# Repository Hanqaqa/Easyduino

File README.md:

# Easyduino: Repository of Open Source PCB Devboards for KiCad

The Easyduino project is an effort to easily dive into different PCB designs of the most popular microcontroller devboards like **Arduino, ESP32, Raspberry Pico and STM32 Bluepill** (more to come!). Using the free and Open Source Software [KiCad](https://www.kicad.org/) and adhering the best practices across the PCB and KiCad ecosystem. Also adding the much needed USB-C support!

The project was born out of the necessity to unify the wide variety of software, languages and conventions used in the most popular devboards. For example Arduino Uno was developed in 2010, Italy, using Eagle. The ESP32 devboard was developed in 2016, China, using Altium. The Raspberry Pi Pico 2040 was developed around 2021 in the U.K. using KiCad and Altium...

## Available Development Boards 

[Easyduino UNO](https://github.com/Hanqaqa/Easyduino/tree/master/Atmega328p%20Arduino%20Uno) | [Easyduino Nano](https://github.com/Hanqaqa/Easyduino/tree/master/Atmega328p%20Arduino%20Nano) | [Easyduino ESP32](https://github.com/Hanqaqa/Easyduino/tree/master/ESP32) |
---|---|---|
 |  |  | 

[Easyduino ESP32 S3](https://github.com/Hanqaqa/Easyduino/tree/master/ESP32S3) | [Easyduino Pi Pico](https://github.com/Hanqaqa/Easyduino/tree/master/Raspberry%20Pi%20Pico%202040) | [Easyduino Bluepill STM32F103](https://github.com/Hanqaqa/Easyduino/tree/master/STM32F103%20Bluepill)
---|---|---|
 |  | 

[Easyduino Pi Pico 2](https://github.com/Hanqaqa/Easyduino/tree/master/PiPico2) | [Easyduino Pi Pico 2 2354B](https://github.com/Hanqaqa/Easyduino/tree/master/PiPico22354B) | [Easyduino nrf52840 dongle](https://github.com/Hanqaqa/Easyduino/tree/master/nrf52840dongle)
---|---|---|
 |  | 

The outline, pinout, layout and components have been tried to be replicated with respect to the originals, in all of the boards. With various levels of success. 

Some boards, like the Raspberry Pi Pico use 01005 components which are too expensive for the manufacturer to integrate in the PCB Aseembly line. Some other components like the original Arduino UNO USB to Serial converter, an Atmega16u2, were hard to come by during the development of this project ~January 2023, so more readily available options were chosen. All the differences with the original boards are explained inside the folder of each project in a readme file. 

4 layers of copper have been used in all projects to simplify the wiring. Specifically the [JLC04161H-7628](https://jlcpcb.com/impedance) stackup. 

The PCB constraints of the manufacturer JLCPCB are explained [here](https://github.com/Hanqaqa/Easyduino/tree/master/Assets/JLCPCB%20Constraints)

## Structure of each project

Each project consists of: 
- Main KiCad files (.kicad_pro, .kicad_sch...)
- A readme explaining the specifics of that project
- xxx.pretty or xxxlibraries folder which contains the non standard footprints or schematic parts used in the project (Some projects such as the Arduino UNO only use standard libraries, therefore these folders don't exist)
- The **Outputs** folder: Contains all the data produced by the KiCad Jobset like Gerbers, STEPs, PDFs, ERC, BOM, CPLs... Most of these are then copied, organized, and placed into their respective `ProductionFiles` folders.
- The ***ProductionFiles*** folder which includes files such as:
    - BOM: This folder contains both the list of components and the Centroid File in JLCPCB readable format. The CPL .csv file needs a small tweak at the beginning of the file in order to be readable. I mention it [here](https://github.com/Hanqaqa/Easyduino/tree/master/Assets/JLCPCB%20Constraints#cpl-component-placement-list).
    - ***Datasheets***: all the datasheets of the main components used in the project. Datasheets of easily replaceable components such as Resistors, Capacitors and LEDs are not given
    - Gerbers: A zip file with all of the manufacturing gerber files such as Copper/Mask/Silkscreen layers
    - PDFs: PDF and PNG files of the Schematic and PCB
    - Photos: Some photos of the manufactured PCB as well as some renders

## Using the project

1. Install the latest version of [KiCad](https://www.kicad.org/)
2. If you already have KiCad installed, click the upper right button in this github page `<>Code`, click `Download ZIP`, extract the files in your desired folder. If you know how to use git, clone the repository
3. Double click on the xxx.kicad_pro file inside any project and KiCad will start

This project was developed using KiCad v8.0.0, but has been updated and tested with KiCad v10. Including the creation of Jobsets which massively simplfies creating gerbers and BOMs. 

Since this is a collection of projects, the new KiCad v10 Git utilities don't work properly with each project, forcing you to git add the whole project if you want to make a change.

If you'd rather just consult the schematics or the gerbers. They are located inside the **ProductionFiles** folder of each project. Inside the **PDFs** and **Gerber** folders.

## Contributing

If you spot any mistakes inside any of the projects. Either open an issue and I will try to correct it or fork and merge the correction. 

If you plan on developing any other development boards and wish to merge into the project. Please try to use the same style and conventions as the original ones in the schematic. Positive voltages facing up, text being clearly readable, a references page, similar folder structure.

To do list:

- [ ] ~~Order and test the v1.1 RP2040 board. (In v1.0 I mixed some pins in the Flash and couldn't boot up). Ordered. Awaiting arrival. v1.1 is working correctly. Need to update photos and repo.~~ Order v1.2 with Silkscreen text for BOOTSEL and RESET. Once received test and make photos.
- [ ] ~~Order and test the v1.1 ESP32S3 board. (In v1.0 I forgot to add PullUp and PullDown in RST and SUSPEND CP2102). Ordered. Awaiting arrival.~~ TX and RX signals going into CP2102 were mixed. Fix it and order v1.2. Once received test and make photos.
- [ ] Developing: nRF52840 Dongle, RP2350A (Pi Pico 2), and Pi Pico 2 2354B with extra functionalities
- [ ] Investigate other possible microcontrollers/SOCs/FPGAs to implement.

## Acknowledgments

Thanks to [winsrrow](https://github.com/winsrrow) for providing lots of KiCad tips and designing from the ground up the v1.1 RP2040 board.

## Licensing

This project is distributed under the [**CERN Open Hardware Licence Version 2 - Permissive**](https://github.com/Hanqaqa/Easyduino/blob/master/License.txt) which means **you are free to use any or all parts of this project with or without disclosing the source**, even for comercial projects. As long as you include a copy of the CERN OHLv2 Permissive Licence.

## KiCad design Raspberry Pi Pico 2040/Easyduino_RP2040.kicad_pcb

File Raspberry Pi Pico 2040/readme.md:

# Raspberry Pi Pico RP2040 v1.2 IN PROGRESS.

The new and easy to use Microcontroller from the Raspberry Pi Foundation. Now with a Reset button. Connect via USB, hold BOOTSEL (BT), press and release RESET(RST), then release BOOTSEL. You are now in Bootloader mode.

**The pictured version is v1.0 which had some pins mixed up in the flash memory and couldn't boot up. The project contains the v1.2 which corrects that mistake, adds a debug port and some test points. The photo will be updated when I receive and test the new board.**
**The mounting holes are not exactly in the same position as the original Pi Pico due to the size of USBC**

## Schematic

KiCad's "Net classes" have been used in this schematic (The squares and romboids in the schematic). Net classes are useful for organising different nets on the circuit. For example, you can change all tracks widths for that net in just one menu.

## Gerbers

## Specs

- Input Voltage: 5.5V-9V(External Source 5V) or 5V (USB). ONLY USE ONE VOLTAGE INPUT AT A TIME
- Maximum Output Current at 5V input : 200 mA at 3.3V output
- No Polarity Protection (External Source)
- Overcurrent Protection: None! 

## References 

### RP2040

- RPI Pico Schematic
- Hardware design with rp2040 p10 -> 12MHz crystal with 27 pF Capacitors 
- rp2040 datasheet p13 -> USB_DP and USB_DM need 27 Ohm Resistors
- rp2040 datasheet p13 -> Use a 12MHz Crystal
- rp2040 datasheet p13 -> TESTEN to GND
- rp2040 datasheet p155 -> USB_VDD connected to 3.3V and decoupled with a 100 nF capacitor
- rp2040 datasheet p155 -> IOVDD connected to 3.3V and decoupled with a 100 nF capacitor per pin (6pins)
- rp2040 datasheet p155 -> DVDD connected to VREG_VOUT = 1.1V and decoupled with a 100 nF capacitor per pin (2pins)
- rp2040 datasheet p156 -> ADC_AVDD connected to 3.3V and decoupled with a 100 nF capacitor. A better circuit (Pico Schematic) can be made when ADC is crucial
- rp2040 datasheet p160 -> VREG_VIN Internal 1.1V Voltage regulator Input. Connect to external 3.3V and decouple with 1uF
- rp2040 datasheet p160 -> VREG_VOUT Internal 1.1V Voltage regulator Output. Connect to 1.1V and decouple with 1uF

### USB-C

#### Differential Pair

- USB needs 90 Ohm differential traces. 
- According to JLCPCB impedance calculator, with a JLC7628 prepreg and 6mil (0.15mm) space between lines
- I have to use 9 mil tracks -> 0.2 mm
- I have to place vias because of the pinout of USB C and CP2102. Some other people have done it with no problems

### W25Q16JVUXIQ

- W25Q16JVUXIQ Datasheet p6 -> Use a 100nF and 1uF capacitor
- RPI Pico Schematic -> Use a 100nF and 2uF decoupling capacitors. A pull up resistor is not fitted
- Hardware design with rp2040 p9 -> Use a 100nF decoupling capacitor. Pull up resistor is not fitted, the flash can work without it. 
- I will only place the 100nF capacitor, since the devboard can work according to Hardware design guide. I will not place a pull up resitor

### XC6206P332MR-3.3V

- XC6206_Torex Datasheet p6 -> Two 1 uF ceramic capacitors on Vin and Vout

### Differences with Original Raspberry Pi Pico

- GPIO23 is not exposed or used. Since the voltage regulator used (XC6206...) doesn't have a Power Select mode
- GPIO29_ADC which is used for monitoring VSys (external battery) is not exposed or used in order to save costs
- In the Raspberry Pi Pico Schematic, 2uF capacitors are used for decoupling. I use 1uF decoupling capacitors as indicated in the rp2040 datasheet
- ADC_AVDD is powered only by 3.3V, no option for external Analog powering. This will be more noisy for projects where ADC is used. But in order to save space and cost. I will skip the option to power ADC_AVDD externally

## KiCad Render

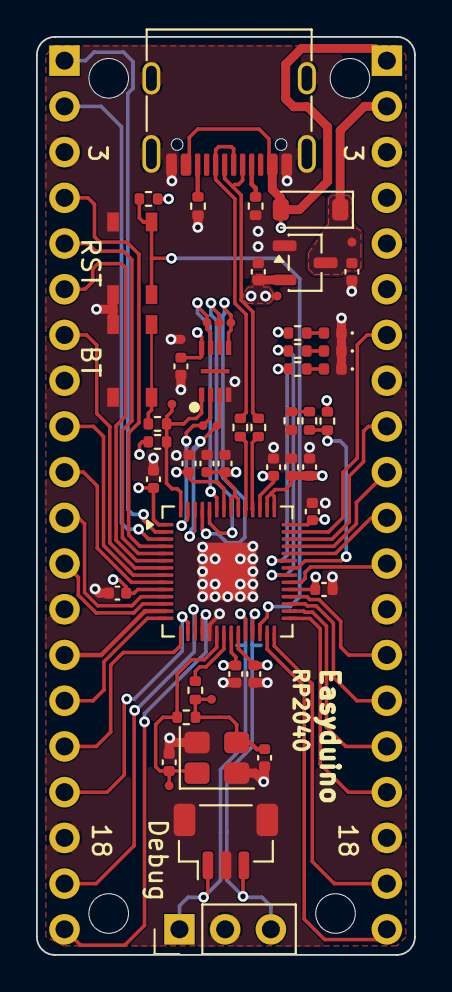
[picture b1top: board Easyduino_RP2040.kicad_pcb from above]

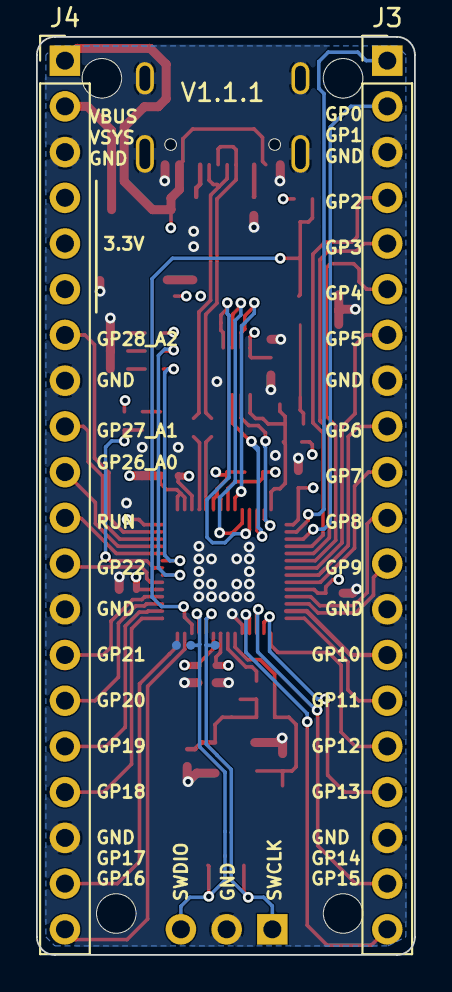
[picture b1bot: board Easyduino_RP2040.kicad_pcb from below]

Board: 4 copper layers, 21.0 x 51.0 mm, 65 parts (5 on the bottom side), 58 nets.

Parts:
C1, C2, C5, C6, C7, C8, C9, C10, C11, C12, C15: 100nF; C_0402_1005Metric
C3, C4, C13, C14: 1uF; C_0402_1005Metric
C16, C17: 27p; C_0402_1005Metric
D1: D_Schottky; D_SOD-123
D2, D3, D4: LED; LED_0402_1005Metric
H1, H2, H3, H4: MountingHole; MountingHole_2.2mm_M2
J1: USB_C_Receptacle_USB2.0; USB_C_Receptacle_G-Switch_GT-USB-7010ASV
J3, J4: Conn_01x20; PinHeader_1x20_P2.54mm_Vertical
J5: Conn_01x03; PinHeader_1x03_P2.54mm_Vertical
J6: Conn_01x03_MountingPin; JST_SH_BM03B-SRSS-TB_1x03-1MP_P1.00mm_Vertical
R1, R2, R3, R6, R7: 5.1k; R_0402_1005Metric
R4, R5: 27R; R_0402_1005Metric
R8, R9, R10, R11, R12, R13, R14, R15: 1k; R_0402_1005Metric
SW1, SW2: SW_Push; ALPSALPINE_SKRPACE010
TP1, TP2, TP3, TP4, TP5, TP6, TP7, TP8, TP9, TP10, TP11, TP12, TP13, TP14: TestPoint_pad
U1: XC6206P332MR; SOT-23-3
U2: RP2040; QFN-56-1EP_7x7mm_P0.4mm_EP3.2x3.2mm
U3: W25Q16JVUXIQ
Y1: 12MHz; Crystal_SMD_3225-4Pin_3.2x2.5mm

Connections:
+1V1: C1.1, C2.1, C3.1, U2.23 (DVDD), U2.45 (VREG_VOUT), U2.50 (DVDD)
+3.3V: C4.1, C5.1, C6.1, C7.1, C8.1, C9.1, C10.1, C11.1, C12.1, C14.1, C15.1, J4.4, J4.5, J4.6, R10.1, R11.1, R12.1, TP2.1 (1_1), U1.2 (VO), U2.1 (IOVDD), U2.10 (IOVDD), U2.22 (IOVDD), U2.33 (IOVDD), U2.42 (IOVDD), U2.43 (ADC_AVDD), U2.44 (VREG_IN), U2.48 (USB_VDD), U2.49 (IOVDD), U3.8 (VCC)
/CC1: J1.A5 (CC1), R1.1
/CC2: J1.B5 (CC2), R2.1
/GPIO0: J3.1, U2.2 (GPIO0)
/GPIO1: J3.2, U2.3 (GPIO1)
/GPIO2: J3.4, U2.4 (GPIO2)
/GPIO3: J3.5, U2.5 (GPIO3)
/GPIO4: J3.6, U2.6 (GPIO4)
/GPIO5: J3.7, U2.7 (GPIO5)
/GPIO6: J3.9, U2.8 (GPIO6)
/GPIO7: J3.10, U2.9 (GPIO7)
/GPIO8: J3.11, U2.11 (GPIO8)
/GPIO9: J3.12, U2.12 (GPIO9)
/GPIO10: J3.14, U2.13 (GPIO10)
/GPIO11: J3.15, U2.14 (GPIO11)
/GPIO12: J3.16, U2.15 (GPIO12)
/GPIO13: J3.17, U2.16 (GPIO13)
/GPIO14: J3.19, U2.17 (GPIO14)
/GPIO15: J3.20, U2.18 (GPIO15)
/GPIO16: J4.20, U2.27 (GPIO16)
/GPIO17: J4.19, U2.28 (GPIO17)
/GPIO18: J4.17, U2.29 (GPIO18)
/GPIO19: J4.16, U2.30 (GPIO19)
/GPIO20: J4.15, U2.31 (GPIO20)
/GPIO21: J4.14, U2.32 (GPIO21)
/GPIO22: J4.12, U2.34 (GPIO22)
/GPIO23: R13.1, U2.35 (GPIO23)
/GPIO24: R3.1, R6.2, U2.36 (GPIO24)
/GPIO25: R14.1, U2.37 (GPIO25)
/GPIO26_ADC0: J4.11, U2.38 (GPIO26_ADC0)
/GPIO27_ADC1: J4.10, U2.39 (GPIO27_ADC1)
/GPIO28_ADC2: J4.9, U2.40 (GPIO28_ADC2)
/GPIO29_ADC3: J4.7, U2.41 (GPIO29_ADC3)
/LED_3V3: D2.2 (A), R12.2
/LED_BUILT_IN1: D4.2 (A), R14.2
/LED_BUILT_IN2: D3.2 (A), R13.2
/QSPI_SCLK: TP9.1 (1_1), U2.52 (QSPI_SCLK), U3.6 (CLK)
/QSPI_SD0: TP10.1 (1_1), U2.53 (QSPI_SD0), U3.5 (DI(IO0))
/QSPI_SD1: TP11.1 (1_1), U2.55 (QSPI_SD1), U3.2 (DO(IO1))
/QSPI_SD2: TP12.1 (1_1), U2.54 (QSPI_SD2), U3.3 (IO2)
/QSPI_SD3: TP13.1 (1_1), U2.51 (QSPI_SD3), U3.7 (IO3)
/QSPI_SS: R10.2, R15.1, TP8.1 (1_1), U2.56 (QSPI_SS), U3.1 (~CS)
/RDIV: R6.1, R7.2
/RUN: R11.2, SW2.2, U2.26 (RUN)
/SW1_{PULL-UP}: R15.2, SW1.2
/SWCLK: J5.1, J6.1, TP5.1 (1_1), U2.24 (SWCLK)
/SWD: J5.3, J6.3, TP6.1 (1_1), U2.25 (SWD)
/USB_DN: J1.A7 (D-), J1.B7 (D-), R5.1
/USB_DP: J1.A6 (D+), J1.B6 (D+), R4.1
/USB_R_DN: R5.2, U2.46 (USB_DM)
/USB_R_DP: R4.2, U2.47 (USB_DP)
/Xin: C16.1, R8.1, TP3.1 (1_1), U2.20 (XIN), Y1.1
/Xout: R9.2, U2.21 (XOUT)
/XoutR: C17.1, R8.2, R9.1, TP4.1 (1_1), Y1.3
GND: C1.2, C2.2, C3.2, C4.2, C5.2, C6.2, C7.2, C8.2, C9.2, C10.2, C11.2, C12.2, C13.2, C14.2, C15.2, C16.2, C17.2, D2.1 (K), D3.1 (K), D4.1 (K), J1.A1 (GND), J1.A12 (GND), J1.B1 (GND), J1.B12 (GND), J1.SH (SHIELD), J3.3, J3.8, J3.13, J3.18, J4.3, J4.8, J4.13, J4.18, J5.2, J6.2, J6.MP (MountPin), R1.2, R2.2, R7.1, SW1.1, SW2.1, TP7.1 (1_1), TP14.1 (1_1), U1.1 (GND), U2.19 (TESTEN), U2.57 (GND), U3.4 (GND), Y1.2 (G), Y1.4 (G)
VBUS: D1.2 (A), J1.A4 (VBUS), J1.A9 (VBUS), J1.B4 (VBUS), J1.B9 (VBUS), J4.1, R3.2
VCC: C13.1, D1.1 (K), J4.2, TP1.1 (1_1), U1.3 (VI)

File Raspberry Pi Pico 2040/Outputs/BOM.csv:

"Reference","Value","Qty","#","LCSC"
"C1","100nF","1","1","C1525"
"C2","100nF","1","2","C1525"
"C3","1uF","1","3","C52923"
"C4","1uF","1","4","C52923"
"C5","100nF","1","5","C1525"
"C6","100nF","1","6","C1525"
"C7","100nF","1","7","C1525"
"C8","100nF","1","8","C1525"
"C9","100nF","1","9","C1525"
"C10","100nF","1","10","C1525"
"C11","100nF","1","11","C1525"
"C12","100nF","1","12","C1525"
"C13","1uF","1","13","C52923"
"C14","1uF","1","14","C52923"
"C15","100nF","1","15","C1525"
"C16","27p","1","16","C1557"
"C17","27p","1","17","C1557"
"D1","D_Schottky","1","18","C8598"
"D2","LED","1","19","C434448"
"D3","LED","1","20","C434448"
"D4","LED","1","21","C434448"
"H1","MountingHole","1","22","-"
"H2","MountingHole","1","23","-"
"H3","MountingHole","1","24","-"
"H4","MountingHole","1","25","-"
"J1","USB_C_Receptacle_USB2.0","1","26","C2765186"
"J3","Conn_01x20","1","27","-"
"J4","Conn_01x20","1","28","-"
"J5","Conn_01x03","1","29","-"
"J6","Conn_01x03_MountingPin","1","30","C160389"
"R1","5.1k","1","31","C25905"
"R2","5.1k","1","32","C25905"
"R3","5.1k","1","33","C25905"
"R4","27R","1","34","C2909343"
"R5","27R","1","35","C2909343"
"R6","5.1k","1","36","C25905"
"R7","5.1k","1","37","C25905"
"R9","1k","1","38","C11702"
"R12","1k","1","39","C11702"
"R13","1k","1","40","C11702"
"R14","1k","1","41","C11702"
"R15","1k","1","42","C11702"
"SW1","SW_Push","1","43","C139797"
"SW2","SW_Push","1","44","C139797"
"TP1","","1","45",""
"TP2","","1","46",""
"TP3","","1","47",""
"TP4","","1","48",""
"TP5","","1","49",""
"TP6","","1","50",""
"TP7","","1","51",""
"TP8","","1","52",""
"TP9","","1","53",""
"TP10","","1","54",""
"TP11","","1","55",""
"TP12","","1","56",""
"TP13","","1","57",""
"TP14","","1","58",""
"U1","XC6206P332MR","1","59","C347376"
"U2","RP2040","1","60","C2040"
"U3","W25Q16JVUXIQ","1","61","C2843335"
"Y1","12MHz","1","62","C9002"

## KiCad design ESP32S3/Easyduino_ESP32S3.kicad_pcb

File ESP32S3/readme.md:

# ESP32S3 v1.2 IN PROGRESS

The new and powerful microcontroller from Espressif

**The pictured version is v1.0 which had TX/RX from the CP2102 going into the ESP32S3 module mixed up. The project contains the v1.2 which corrects that mistake. Will update the pictures once I order antoher batch and test everything works correctly.**

## Schematic

KiCad Schematic symbols, footprints and 3D Models were obtained from their [KiCad Github repository](https://github.com/espressif/kicad-libraries)

## Gerbers

## Specs

- Input Voltage: 5V-15V(External Source 5V) 5V (USB UART OR USB ESP32) or 3.3V. ONLY USE ONE VOLTAGE INPUT AT A TIME
- Output Current at 3.3V : 1 A (External Source) 500mA (USB)
- No Polarity Protection (External Source)
- Overcurrent Protection: None 

## References 

### ESP32 S3 WROOM 1

#### Decoupling Capacitors:

- ESP32 S3 WROOM 1 datasheet p25 -> 3.3V pin needs a 22uF and a 100nF capacitors. The 22uF doesn't have to be a tantalum capacitor. But I will use a tantalum to reuse components

#### Automatic Bootloader

- ESPS3 Sch -> Automatic Bootloader.
- ESPS3 Sch / ESP32 S3 WROOM 1 datasheet p25 -> EN pin 10k resistor and 100nF capacitor

#### Thermal vias

- ESP32 S3 WROOM 1 datasheet p27 -> GND Thermal needs vias between pads

### USB-C

#### Filtering 

- USB Hardware Design Guidelines for FTDI ICs p8 -> 10nF Cap + Ferrite Bead + 100nF Cap + 4.7uF Cap
- I disregarded such heavy filtering for the easier to implement 1uF and 100nF cap given in the CP2102 datasheet
- I added a polyfuse with Ihold=500mA and Itrip=1A.

#### Differential Pair

- USB needs 90 Ohm differential traces. 
- Using JLCPCB's JLC04161H-7628 stackup.
- Which with Signal Layer (Layer 1) and a GND layer (L2) below. And with 0.2mm tracks and separated 0.15mm gives a differential pair impedance of approximately 90 Ohms.
- For USB1 will use a very short trace for D+ D- (around 2mm)
- For USB2 (tracks that go to the internal ESP32 S3 pins and the pinout) the traces are long ~60mm for D+ D-, and have vias
- The Development board from ESP32S3 has no problem with these differential pairs with vias and is a 2 board layer
- I also have to place vias because of the pinout of USB C and CP2102. Some other people have placed vias without problems for signal integrity

#### CP2102

- CP2102 datasheet p15 -> VBUS will be tied to REGIN. 1uF and 100 nF will be added.
- CP2102 datasheet p15 -> ESD Supression Diode for all three inputs of USB  
- CP2102 datasheet p15 and p19 -> 100nF for VDD output, 4.7 uF is optional for higher current circuits.
- CP2102 datasheet p23 -> The VDD or 3.3 output can only provide 100mA. I will not use this as a voltage provider for the ciruit. I will use the AMS1117-3.3 
- CP2102 datasheet p15 -> RST pulled up via 4.7k and SUSPEND~ pulled down via 10k.

#### AMS1117-3.3V

- AMS1117 Datasheet p1 -> 3.3V/1A Output with 5-15V Input
- AMS1117 Datasheet p4 -> 22uF tantalum capacitor on input and output.

## KiCad Render

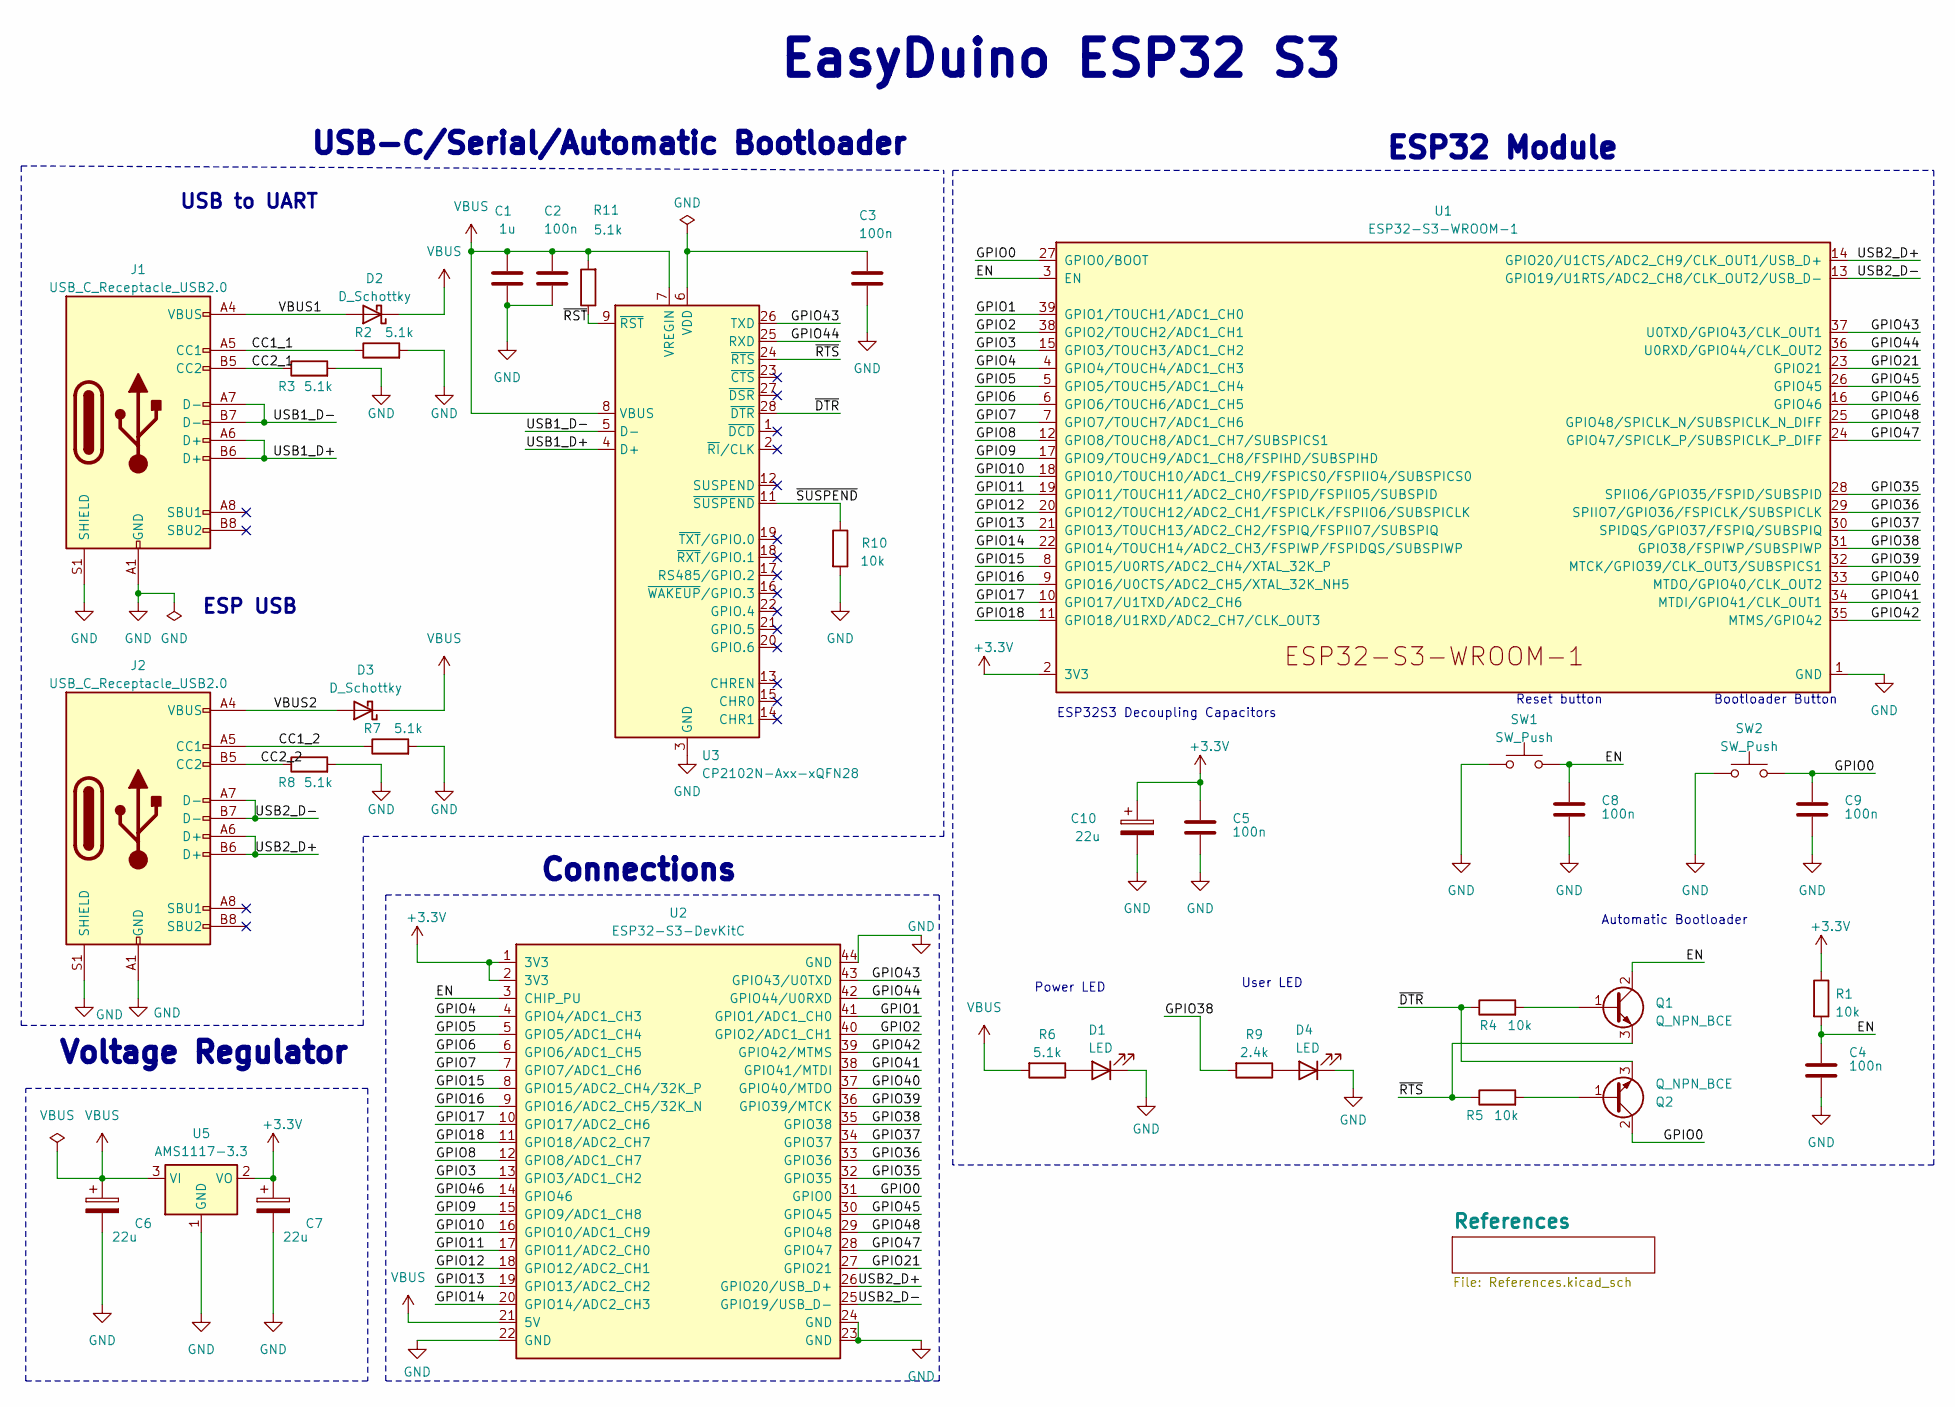
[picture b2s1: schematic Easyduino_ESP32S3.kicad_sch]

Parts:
C1: 1u; C_0402_1005Metric; LCSC C52923
C2, C3, C4, C5, C8, C9: 100n; C_0402_1005Metric; LCSC C1525
C6, C7, C10: 22u; CP_EIA-3216-10_Kemet-I; LCSC C11366
D1, D4: LED; LED_0402_1005Metric; LCSC C434447
D2, D3: D_Schottky; D_0402_1005Metric; LCSC C2837790
J1, J2: USB_C_Receptacle_USB2.0; USB_C_Receptacle_G-Switch_GT-USB-7010ASV; LCSC C2765186
Q1, Q2: Q_NPN_BCE; SOT-23W; LCSC C916392
R1, R4, R5, R10: 10k; R_0402_1005Metric; LCSC C25744
R2, R3, R6, R7, R8, R11: 5.1k; R_0402_1005Metric; LCSC C25905
R9: 2.4k; R_0402_1005Metric; LCSC C25882
SW1, SW2: SW_Push; SW_Push_SPST_NO_Alps_SKRK; LCSC C720477
U1: ESP32-S3-WROOM-1; LCSC C2913197
U2: ESP32-S3-DevKitC
U3: CP2102N-Axx-xQFN28; QFN-28-1EP_5x5mm_P0.5mm_EP3.35x3.35mm; LCSC C6568
U5: AMS1117-3.3; SOT-223-3_TabPin2; LCSC C6186

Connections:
+3.3V: C5.1, C7.1, C10.1, R1.1, U1.2 (3V3), U2.1 (3V3), U2.2 (3V3), U5.2 (VO)
/CC1_1: J1.A5 (CC1), R2.1
/CC1_2: J2.A5 (CC1), R7.1
/CC2_1: J1.B5 (CC2), R3.1
/CC2_2: J2.B5 (CC2), R8.1
/EN: C4.1, C8.1, Q1.2 (C), R1.2, SW1.2, U1.3 (EN), U2.3 (CHIP_PU)
/GPIO0: C9.1, Q2.2 (C), SW2.2, U1.27 (GPIO0/BOOT), U2.31 (GPIO0)
/GPIO1: U1.39 (GPIO1/TOUCH1/ADC1_CH0), U2.41 (GPIO1/ADC1_CH0)
/GPIO2: U1.38 (GPIO2/TOUCH2/ADC1_CH1), U2.40 (GPIO2/ADC1_CH1)
/GPIO3: U1.15 (GPIO3/TOUCH3/ADC1_CH2), U2.13 (GPIO3/ADC1_CH2)
/GPIO4: U1.4 (GPIO4/TOUCH4/ADC1_CH3), U2.4 (GPIO4/ADC1_CH3)
/GPIO5: U1.5 (GPIO5/TOUCH5/ADC1_CH4), U2.5 (GPIO5/ADC1_CH4)
/GPIO6: U1.6 (GPIO6/TOUCH6/ADC1_CH5), U2.6 (GPIO6/ADC1_CH5)
/GPIO7: U1.7 (GPIO7/TOUCH7/ADC1_CH6), U2.7 (GPIO7/ADC1_CH6)
/GPIO8: U1.12 (GPIO8/TOUCH8/ADC1_CH7/SUBSPICS1), U2.12 (GPIO8/ADC1_CH7)
/GPIO9: U1.17 (GPIO9/TOUCH9/ADC1_CH8/FSPIHD/SUBSPIHD), U2.15 (GPIO9/ADC1_CH8)
/GPIO10: U1.18 (GPIO10/TOUCH10/ADC1_CH9/FSPICS0/FSPIIO4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), U2.16 (GPIO10/ADC1_CH9)
/GPIO11: U1.19 (GPIO11/TOUCH11/ADC2_CH0/FSPID/FSPIIO5/S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), U2.17 (GPIO11/ADC2_CH0)
/GPIO12: U1.20 (GPIO12/TOUCH12/ADC2_CH1/FSPICLK/FSPIIO6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), U2.18 (GPIO12/ADC2_CH1)
/GPIO13: U1.21 (GPIO13/TOUCH13/ADC2_CH2/FSPIQ/FSPIIO7/S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), U2.19 (GPIO13/ADC2_CH2)
/GPIO14: U1.22 (GPIO14/TOUCH14/ADC2_CH3/FSPIWP/FSPIDQS/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), U2.20 (GPIO14/ADC2_CH3)
/GPIO15: U1.8 (GPIO15/U0RTS/ADC2_CH4/XTAL_32K_P), U2.8 (GPIO15/ADC2_CH4/32K_P)
/GPIO16: U1.9 (GPIO16/U0CTS/ADC2_CH5/XTAL_32K_NH5), U2.9 (GPIO16/ADC2_CH5/32K_N)
/GPIO17: U1.10 (GPIO17/U1TXD/ADC2_CH6), U2.10 (GPIO17/ADC2_CH6)
/GPIO18: U1.11 (GPIO18/U1RXD/ADC2_CH7/CLK_OUT3), U2.11 (GPIO18/ADC2_CH7)
/GPIO21: U1.23 (GPIO21), U2.27 (GPIO21)
/GPIO35: U1.28 (SPIIO6/GPIO35/FSPID/SUBSPID), U2.32 (GPIO35)
/GPIO36: U1.29 (SPIIO7/GPIO36/FSPICLK/SUBSPICLK), U2.33 (GPIO36)
/GPIO37: U1.30 (SPIDQS/GPIO37/FSPIQ/SUBSPIQ), U2.34 (GPIO37)
/GPIO38: R9.2, U1.31 (GPIO38/FSPIWP/SUBSPIWP), U2.35 (GPIO38)
/GPIO39: U1.32 (MTCK/GPIO39/CLK_OUT3/SUBSPICS1), U2.36 (GPIO39/MTCK)
/GPIO40: U1.33 (MTDO/GPIO40/CLK_OUT2), U2.37 (GPIO40/MTDO)
/GPIO41: U1.34 (MTDI/GPIO41/CLK_OUT1), U2.38 (GPIO41/MTDI)
/GPIO42: U1.35 (MTMS/GPIO42), U2.39 (GPIO42/MTMS)
/GPIO43: U1.37 (U0TXD/GPIO43/CLK_OUT1), U2.43 (GPIO43/U0TXD), U3.26 (TXD)
/GPIO44: U1.36 (U0RXD/GPIO44/CLK_OUT2), U2.42 (GPIO44/U0RXD), U3.25 (RXD)
/GPIO45: U1.26 (GPIO45), U2.30 (GPIO45)
/GPIO46: U1.16 (GPIO46), U2.14 (GPIO46)
/GPIO47: U1.24 (GPIO47/SPICLK_P/SUBSPICLK_P_DIFF), U2.28 (GPIO47)
/GPIO48: U1.25 (GPIO48/SPICLK_N/SUBSPICLK_N_DIFF), U2.29 (GPIO48)
/USB1_D+: J1.A6 (D+), J1.B6 (D+), U3.4 (D+)
/USB1_D-: J1.A7 (D-), J1.B7 (D-), U3.5 (D-)
/USB2_D+: J2.A6 (D+), J2.B6 (D+), U1.14 (GPIO20/U1CTS/ADC2_CH9/CLK_OUT1/USB_D+), U2.26 (GPIO20/USB_D+)
/USB2_D-: J2.A7 (D-), J2.B7 (D-), U1.13 (GPIO19/U1RTS/ADC2_CH8/CLK_OUT2/USB_D-), U2.25 (GPIO19/USB_D-)
/VBUS1: D2.2 (A), J1.A4 (VBUS), J1.A9 (VBUS), J1.B4 (VBUS), J1.B9 (VBUS)
/VBUS2: D3.2 (A), J2.A4 (VBUS), J2.A9 (VBUS), J2.B4 (VBUS), J2.B9 (VBUS)
/~DTR: Q2.3 (E), R4.1, U3.28 (~DTR)
/~RST: R11.1, U3.9 (~RST)
/~RTS: Q1.3 (E), R5.1, U3.24 (~RTS)
/~SUSPEND: R10.1, U3.11 (~SUSPEND)
GND: C1.2, C2.2, C3.2, C4.2, C5.2, C6.2, C7.2, C8.2, C9.2, C10.2, D1.1 (K), D4.1 (K), J1.A1 (GND), J1.A12 (GND), J1.B1 (GND), J1.B12 (GND), J1.S1 (SHIELD), J2.A1 (GND), J2.A12 (GND), J2.B1 (GND), J2.B12 (GND), J2.S1 (SHIELD), R2.2, R3.2, R7.2, R8.2, R10.2, SW1.1, SW2.1, U1.1 (GND), U1.40 (GND), U1.41 (GND), U2.22 (GND), U2.23 (GND), U2.24 (GND), U2.44 (GND), U3.3 (GND), U3.29 (GND), U5.1 (GND)
unnamed: D1.2 (A), R6.1
unnamed: D4.2 (A), R9.1
unnamed: Q1.1 (B), R4.2
unnamed: Q2.1 (B), R5.2
unnamed: C3.1, U3.6 (VDD)
VBUS: C1.1, C2.1, C6.1, D2.1 (K), D3.1 (K), R6.2, R11.2, U2.21 (5V), U3.7 (VREGIN), U3.8 (VBUS), U5.3 (VI)

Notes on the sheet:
Automatic Bootloader
ESP USB
Power LED
ESP32 Module
User LED
USB-C/Serial/Automatic Bootloader
ESP32S3 Decoupling Capacitors
Connections
USB to UART
Voltage Regulator
Bootloader Button
EasyDuino ESP32 S3
Reset button

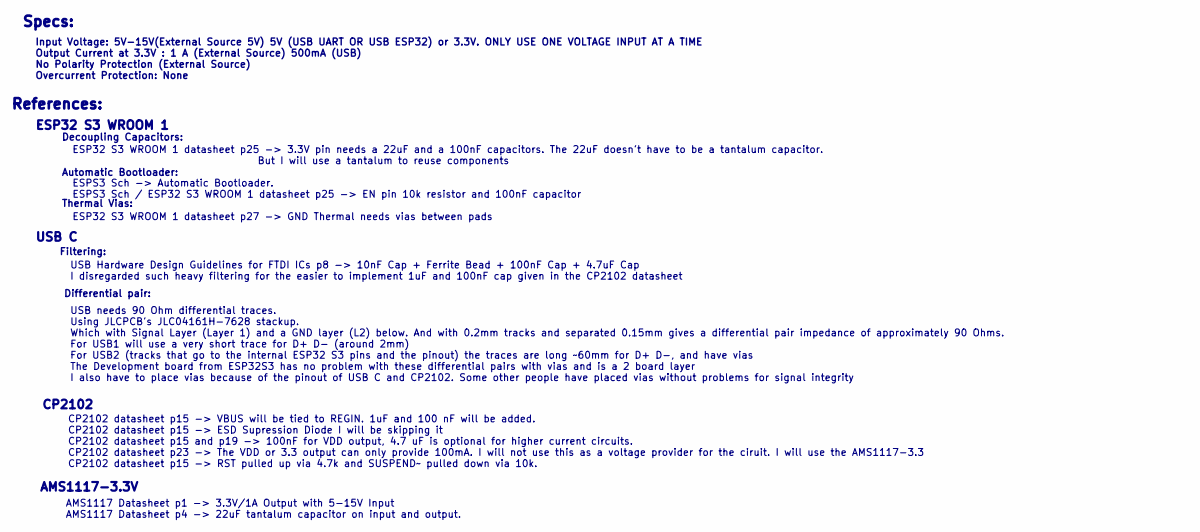
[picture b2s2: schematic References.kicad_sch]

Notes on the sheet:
Filtering:
Input Voltage: 5V-15V(External Source 5V) 5V (USB UART OR USB ESP32) or 3.3V. ONLY USE ONE VOLTAGE INPUT AT A TIME Output Current at 3.3V : 1 A (External Source) 500mA (USB) No Polarity Protection (External Source) Overcurrent Protection: None
Thermal Vias:
References:
ESP32 S3 WROOM 1
ESP32 S3 WROOM 1 datasheet p25 -> 3.3V pin needs a 22uF and a 100nF capacitors. The 22uF doesn't have to be a tantalum capacitor. But I will use a tantalum to reuse components ESPS3 Sch -> Automatic Bootloader. ESPS3 Sch / ESP32 S3 WROOM 1 datasheet p25 -> EN pin 10k resistor and 100nF capacitor ES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
Specs:
USB C
AMS1117-3.3V
CP2102 datasheet p15 -> VBUS will be tied to REGIN. 1uF and 100 nF will be added. CP2102 datasheet p15 -> ESD Supression Diode I will be skipping it CP2102 datasheet p15 and p19 -> 100nF for VDD output, 4.7 uF is optional for higher current circuits. CP2102 datasheet p23 -> The VDD or 3.3 output ca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
AMS1117 Datasheet p1 -> 3.3V/1A Output with 5-15V Input AMS1117 Datasheet p4 -> 22uF tantalum capacitor on input and output.
CP2102
Decoupling Capacitors:
USB needs 90 Ohm differential traces. Using JLCPCB's JLC04161H-7628 stackup. Which with Signal Layer (Layer 1) and a GND layer (L2) below. And with 0.2mm tracks and separated 0.15mm gives a differential pair impedance of approximately 90 Ohms. For USB1 will use a very short trace for D+ D- (around 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
Automatic Bootloader:
USB Hardware Design Guidelines for FTDI ICs p8 -> 10nF Cap + Ferrite Bead + 100nF Cap + 4.7uF Cap I disregarded such heavy filtering for the easier to implement 1uF and 100nF cap given in the CP2102 datasheet
Differential pair:

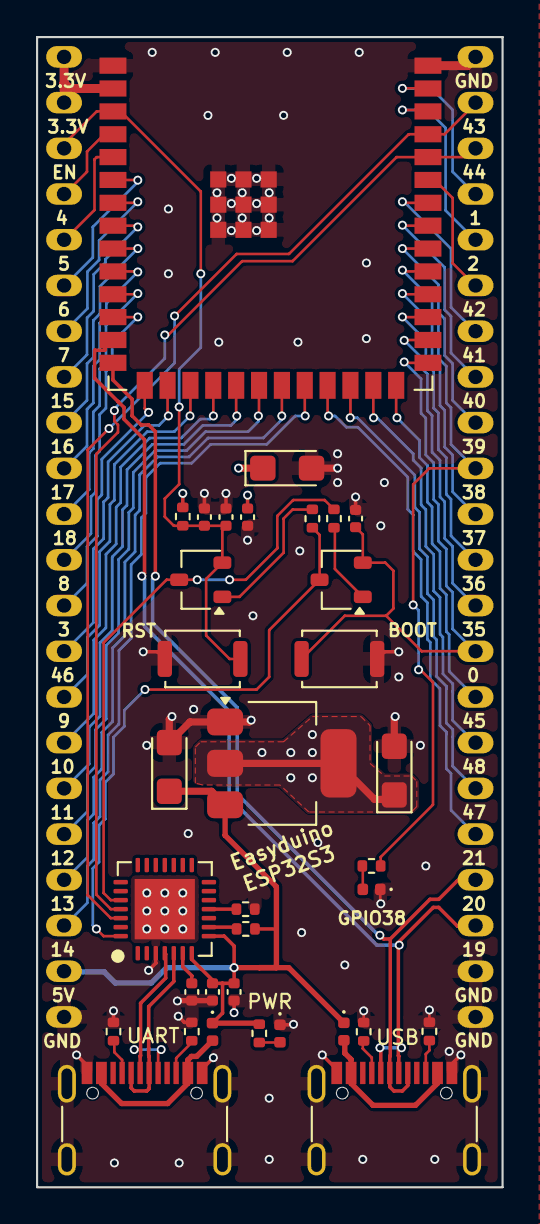
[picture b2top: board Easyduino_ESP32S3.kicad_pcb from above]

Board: 4 copper layers, 25.9 x 63.9 mm, 35 parts (0 on the bottom side), 57 nets.

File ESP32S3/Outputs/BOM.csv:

"Reference","Value","Qty","#","LCSC"
"C1","1u","1","1","C52923"
"C2","100n","1","2","C1525"
"C3","100n","1","3","C1525"
"C4","100n","1","4","C1525"
"C5","100n","1","5","C1525"
"C6","22u","1","6","C11366"
"C7","22u","1","7","C11366"
"C8","100n","1","8","C1525"
"C9","100n","1","9","C1525"
"C10","22u","1","10","C11366"
"D1","LED","1","11","C434447"
"D2","D_Schottky","1","12","C2837790"
"D3","D_Schottky","1","13","C2837790"
"D4","LED","1","14","C434447"
"J1","USB_C_Receptacle_USB2.0","1","15","C2765186"
"J2","USB_C_Receptacle_USB2.0","1","16","C2765186"
"Q1","Q_NPN_BCE","1","17","C916392"
"Q2","Q_NPN_BCE","1","18","C916392"
"R1","10k","1","19","C25744"
"R2","5.1k","1","20","C25905"
"R3","5.1k","1","21","C25905"
"R4","10k","1","22","C25744"
"R5","10k","1","23","C25744"
"R6","5.1k","1","24","C25905"
"R7","5.1k","1","25","C25905"
"R8","5.1k","1","26","C25905"
"R9","2.4k","1","27","C25882"
"SW1","SW_Push","1","28","C720477"
"SW2","SW_Push","1","29","C720477"
"U1","ESP32-S3-WROOM-1","1","30","C2913197"
"U2","ESP32-S3-DevKitC","1","31","-"
"U3","CP2102N-Axx-xQFN28","1","32","C6568"
"U5","AMS1117-3.3","1","33","C6186"

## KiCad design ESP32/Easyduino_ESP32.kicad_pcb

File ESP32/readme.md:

# ESP32

The most popular WiFi Microcontroller

## Schematic

KiCad Schematic symbols, footprints and 3D Models were obtained from their [KiCad Github repository](https://github.com/espressif/kicad-libraries)

## Gerbers

## Specs

- Input Voltage: 5V-15V(External Source 5V Pin) 5V (USB) or 3.3V (3.3V Pin). ONLY USE ONE VOLTAGE INPUT AT A TIME
- Output Current at 3.3V : 1 A (External Source) 500mA (USB)
- No Polarity Protection (External Source)
- Overcurrent Protection: None 

## References 

### ESP32 WROOM 32E

#### Decoupling capacitors 

- ESP32 Wroom 32 E datasheet p24 -> 3.3V pin needs one 22uF and one 100nF capacitors

#### Enable pin (EN)

- ESP32 Devkit sch -> EN pin 10k resistor and 100nF capacitor

#### Thermal Pad

- ESP32 Wroom 32 E datasheet p26 -> GND Thermal needs vias between pads. Needed vias are too small for my manufacturer. I will use bigger vias

#### Automatic Bootloader

- ESP32 Devkit sch -> Automatic Bootloader.

### USB-C

#### Filtering 

- USB Hardware Design Guidelines for FTDI ICs p8 -> 10nF Cap + Ferrite Bead + 100nF Cap + 4.7uF Cap
- I disregarded such heavy filtering for the easier to implement 1uF and 100nF cap given in the CP2102 datasheet
- I added a polyfuse with Ihold=500mA and Itrip=1A.

#### Differential Pair

- USB needs 90 Ohm differential traces. 
- According to JLCPCB impedance calculator, with a JLC7628 prepreg and 6mil (0.15mm) space between lines
- I have to use 9 mil tracks -> 0.2 mm
- I will use a very short trace for D+ D- (around 2mm)
- I have to place vias because of the pinout of USB C and CP2102. Some other people have done it with no problems

#### CP2102

- CP2102 datasheet p15 -> VBUS will be tied to REGIN. 1uF and 100 nF will be added.
- CP2102 datasheet p15 -> ESD Supression Diode for all three inputs of USB  
- CP2102 datasheet p15 and p19 -> 100nF for VDD output, 4.7 uF is optional for higher current circuits.
- CP2102 datasheet p23 -> The VDD or 3.3 output can only provide 100mA. I will not use this as a voltage provider for the ciruit. I will use the AMS1117-3.3 
- CP2102 datasheet p15 -> RST pulled up via 4.7k and SUSPEND~ pulled down via 10k.

#### AMS1117-3.3V

- AMS1117 Datasheet p1 -> 3.3V/1A Output with 5-15V Input
- AMS1117 Datasheet p4 -> 22uF tantalum capacitor on input and output.

## KiCad Render

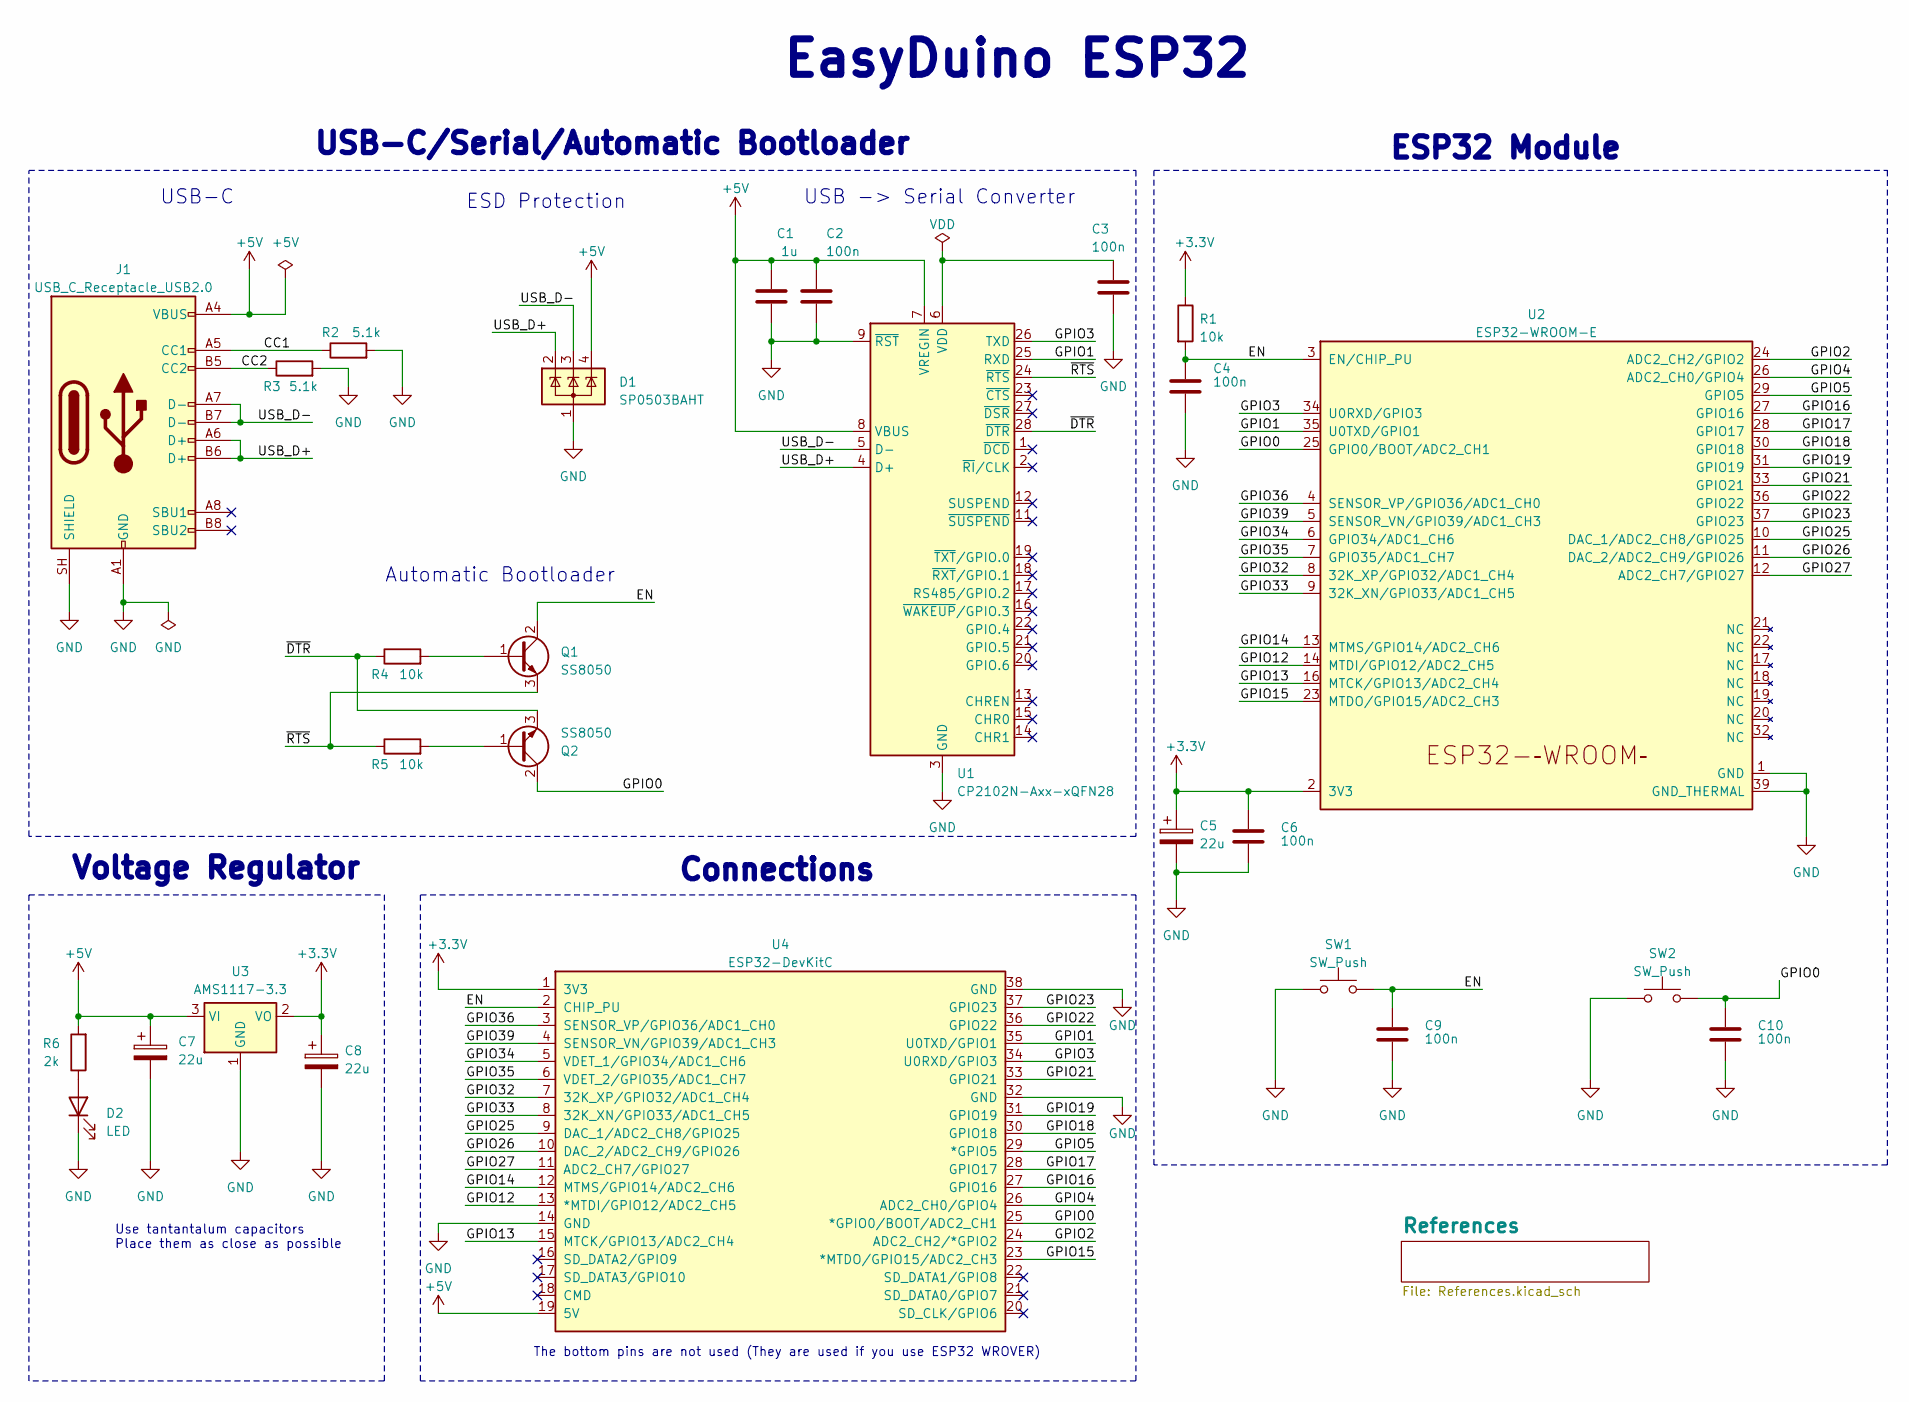
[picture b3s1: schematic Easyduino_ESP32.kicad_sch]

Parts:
C1: 1u; C_0402_1005Metric; LCSC C52923
C2, C3, C4, C6, C9, C10: 100n; C_0402_1005Metric; LCSC C1525
C5, C7, C8: 22u; CP_EIA-3216-10_Kemet-I; LCSC C11366
D1: SP0503BAHT; SOT-143; LCSC C7074
D2: LED; LED_0402_1005Metric; LCSC C434447
J1: USB_C_Receptacle_USB2.0; USB_C_Receptacle_G-Switch_GT-USB-7010ASV; LCSC C2765186
Q1, Q2: SS8050; SOT-23W; LCSC C916392
R1, R4, R5: 10k; R_0402_1005Metric; LCSC C25744
R2, R3: 5.1k; R_0402_1005Metric; LCSC C25905
R6: 2k; R_0402_1005Metric; LCSC C4109
SW1, SW2: SW_Push; SW_Push_SPST_NO_Alps_SKRK; LCSC C720477
U1: CP2102N-Axx-xQFN28; QFN-28-1EP_5x5mm_P0.5mm_EP3.35x3.35mm; LCSC C6568
U2: ESP32-WROOM-E; ESP32-WROOM-32E; LCSC C701342
U3: AMS1117-3.3; SOT-223-3_TabPin2; LCSC C6186
U4: ESP32-DevKitC

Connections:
+3.3V: C5.1, C6.1, C8.1, R1.1, U2.2 (3V3), U3.2 (VO), U4.1 (3V3)
+5V: C1.1, C2.1, C7.1, D1.4 (K), J1.A4 (VBUS), J1.A9 (VBUS), J1.B4 (VBUS), J1.B9 (VBUS), R6.2, U1.7 (VREGIN), U1.8 (VBUS), U3.3 (VI), U4.19 (5V)
/CC1: J1.A5 (CC1), R2.1
/CC2: J1.B5 (CC2), R3.1
/EN: C4.1, C9.1, Q1.2 (C), R1.2, SW1.2, U2.3 (EN/CHIP_PU), U4.2 (CHIP_PU)
/GPIO0: C10.1, Q2.2 (C), SW2.2, U2.25 (GPIO0/BOOT/ADC2_CH1), U4.25 (*GPIO0/BOOT/ADC2_CH1)
/GPIO1: U1.25 (RXD), U2.35 (U0TXD/GPIO1), U4.35 (U0TXD/GPIO1)
/GPIO2: U2.24 (ADC2_CH2/GPIO2), U4.24 (ADC2_CH2/*GPIO2)
/GPIO3: U1.26 (TXD), U2.34 (U0RXD/GPIO3), U4.34 (U0RXD/GPIO3)
/GPIO4: U2.26 (ADC2_CH0/GPIO4), U4.26 (ADC2_CH0/GPIO4)
/GPIO5: U2.29 (GPIO5), U4.29 (*GPIO5)
/GPIO12: U2.14 (MTDI/GPIO12/ADC2_CH5), U4.13 (*MTDI/GPIO12/ADC2_CH5)
/GPIO13: U2.16 (MTCK/GPIO13/ADC2_CH4), U4.15 (MTCK/GPIO13/ADC2_CH4)
/GPIO14: U2.13 (MTMS/GPIO14/ADC2_CH6), U4.12 (MTMS/GPIO14/ADC2_CH6)
/GPIO15: U2.23 (MTDO/GPIO15/ADC2_CH3), U4.23 (*MTDO/GPIO15/ADC2_CH3)
/GPIO16: U2.27 (GPIO16), U4.27 (GPIO16)
/GPIO17: U2.28 (GPIO17), U4.28 (GPIO17)
/GPIO18: U2.30 (GPIO18), U4.30 (GPIO18)
/GPIO19: U2.31 (GPIO19), U4.31 (GPIO19)
/GPIO21: U2.33 (GPIO21), U4.33 (GPIO21)
/GPIO22: U2.36 (GPIO22), U4.36 (GPIO22)
/GPIO23: U2.37 (GPIO23), U4.37 (GPIO23)
/GPIO25: U2.10 (DAC_1/ADC2_CH8/GPIO25), U4.9 (DAC_1/ADC2_CH8/GPIO25)
/GPIO26: U2.11 (DAC_2/ADC2_CH9/GPIO26), U4.10 (DAC_2/ADC2_CH9/GPIO26)
/GPIO27: U2.12 (ADC2_CH7/GPIO27), U4.11 (ADC2_CH7/GPIO27)
/GPIO32: U2.8 (32K_XP/GPIO32/ADC1_CH4), U4.7 (32K_XP/GPIO32/ADC1_CH4)
/GPIO33: U2.9 (32K_XN/GPIO33/ADC1_CH5), U4.8 (32K_XN/GPIO33/ADC1_CH5)
/GPIO34: U2.6 (GPIO34/ADC1_CH6), U4.5 (VDET_1/GPIO34/ADC1_CH6)
/GPIO35: U2.7 (GPIO35/ADC1_CH7), U4.6 (VDET_2/GPIO35/ADC1_CH7)
/GPIO36: U2.4 (SENSOR_VP/GPIO36/ADC1_CH0), U4.3 (SENSOR_VP/GPIO36/ADC1_CH0)
/GPIO39: U2.5 (SENSOR_VN/GPIO39/ADC1_CH3), U4.4 (SENSOR_VN/GPIO39/ADC1_CH3)
/USB_D+: D1.2 (K), J1.A6 (D+), J1.B6 (D+), U1.4 (D+)
/USB_D-: D1.3 (K), J1.A7 (D-), J1.B7 (D-), U1.5 (D-)
/~DTR: Q2.3 (E), R4.1, U1.28 (~DTR)
/~RTS: Q1.3 (E), R5.1, U1.24 (~RTS)
GND: C1.2, C2.2, C3.2, C4.2, C5.2, C6.2, C7.2, C8.2, C9.2, C10.2, D1.1 (A), D2.1 (K), J1.A1 (GND), J1.A12 (GND), J1.B1 (GND), J1.B12 (GND), J1.SH (SHIELD), R2.2, R3.2, SW1.1, SW2.1, U1.3 (GND), U1.9 (~RST), U1.29 (GND), U2.1 (GND), U2.15 (GND), U2.38 (GND), U2.39 (GND_THERMAL), U3.1 (GND), U4.14 (GND), U4.32 (GND), U4.38 (GND)
unnamed: D2.2 (A), R6.1
unnamed: Q1.1 (B), R4.2
unnamed: Q2.1 (B), R5.2
unnamed: C3.1, U1.6 (VDD)

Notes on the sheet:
ESD Protection
ESP32 Module
Voltage Regulator
Use tantantalum capacitors Place them as close as possible
Automatic Bootloader
USB-C
The bottom pins are not used (They are used if you use ESP32 WROVER)
USB -> Serial Converter
USB-C/Serial/Automatic Bootloader
EasyDuino ESP32
Connections
